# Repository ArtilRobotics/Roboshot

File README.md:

RoboShot
======================

Original project
here https://hectorbot.de/

Minimal Requirements 
---
	- RaspberryPi 3
	- Debian bases Linux (to use installscript)
    - Python 3.8

Prepare Raspberry
---
Activate I2C:

    sudo raspi-config 

Here go to "Interfacing Options" and Activate/Enable I2C 

PWM update:
----
Since this library and the onboard Raspberry Pi audio both use the PWM, they cannot be used together. You will need to blacklist the Broadcom audio kernel module by creating a file /etc/modprobe.d/snd-blacklist.conf with:
    blacklist snd_bcm2835

If the audio device is still loading after blacklisting, you may also need to comment it out in the /etc/modules file.

On headless systems you may also need to force audio through hdmi Edit config.txt and add:

    hdmi_force_hotplug=1
    hdmi_force_edid_audio=1
don't force if you have screen with the flex port.

Install on RaspberryPi
----
First you have to clone the github repo of Hector

	git clone https://github.com/H3c702/Hector9000.git

This repository doesn't contain a frontent. To get the original Hector9000 frontend see: 

	https://github.com/H3c702/Hector9000WebUI

To start the Hector software first move into the directory:

	cd Hector9000

Then run this command to setup all necessary tools:

	./setup.sh

Or run it with the option "-c" to preset the mqtt preconfigure for the WebUI

	./setup.sh -c

To start the software run:

	./start.sh

Add Drinks
---

To add a new Drink you have to modify the `drinks.py` file and add a new item into the `drink_list` array formatted as followed:

	{
        "name": "NAME OF DRINK",
        "recipe": [
            ("ingr", "INGREDIENT1", AMOUNT1),
            ("ingr", "INGREDIENT2", AMOUNT2)
        ]	
    }

All strings in `UPPERCASE` are placeholders, all lowercase strings have to be used literally in the definition. The `INGREDIENTx` names are not cleartext but are identifiers referencing into the `ingredients` list below in the same file. The `AMOUNTx` values are numerical values of the corresponding ingredient's amount in grams.

At the moment there are only some ingredients but feel free to put in some new. You can add them in src/Hector/conf/database.py .
Or you can use the WebUI when it is implemented.

A future extension might allow multi-language UIs.

Add Ingredients
---
To edit the Ingredients that can be used you can edit the 
database.py or use the tool in the tools folder.

    python3 Hector9000/tools/Editingredients.py

Assigning valves
---
The available ingredients are also moved to the db and can initial be edited in the databas.py 
or over the WEB UI in the future.

For the meantime you can use the script "SetValveIng.py".

    python3 Hector9000/tools/SetValveIng.py

Development on non-Hector hardware :
---

In the `HectorServer.py` you have to comment line :
	
	#from HectorHardware import HectorHardware as Hector

and uncomment:

	from HectorSimulator import HectorSimulator as Hector

## Info 

If you have some ideas or a fix or something else to make 
Hector better, don't be afraid to send us a pullrequest ;-)

---
Special thanks to
<div>
  <a>
   Hector 9000 Team
	git clone https://github.com/H3c702/Hector9000.git
  </a>

</div>

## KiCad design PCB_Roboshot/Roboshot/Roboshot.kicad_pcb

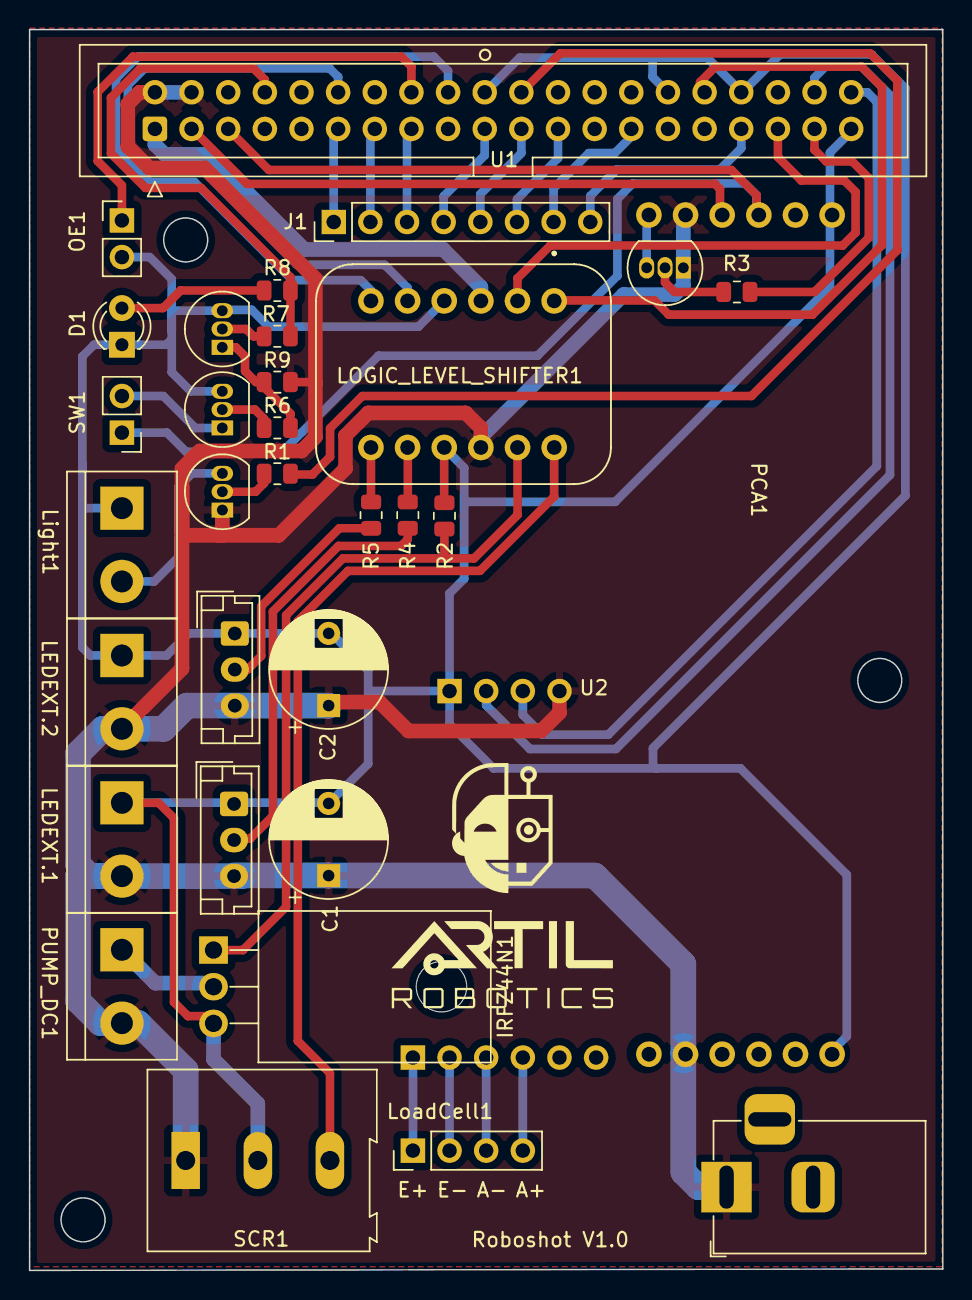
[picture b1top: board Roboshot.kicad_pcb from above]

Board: 2 copper layers, 63.3 x 86.0 mm, 33 parts (0 on the bottom side), 44 nets.

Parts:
B.OUTPUT1: BC546; TO-92_Inline
BUTTON1: BC546; TO-92_Inline
C1, C2: C_Polarized; CP_Radial_D8.0mm_P5.00mm
D1: LED; LED_D3.0mm
Ext.Source1: Conn_01x02; BarrelJack_Horizontal
IRFZ44N1: BSP89; TO-220F-3_Horizontal_TabDown
J1: Conn_01x08; PinHeader_1x08_P2.54mm_Vertical
LEDEXT.1, LEDEXT.2: Conn_01x02; TerminalBlock_bornier-2_P5.08mm
LEDSIGN1, LEDSIGN2: Conn_01x03; JST_EH_B3B-EH-A_1x03_P2.50mm_Vertical
LOGIC_LEVEL_SHIFTER1: Logic_Level_Shifter; Elevador_voltaje
Light1: Conn_01x02; TerminalBlock_bornier-2_P5.08mm
LoadCell1: Conn_01x04; PinHeader_1x04_P2.54mm_Vertical
OE1: Conn_01x02; PinHeader_1x02_P2.54mm_Vertical
PCA1: 815; PCA9685
PUMP_DC1: Conn_01x02; TerminalBlock_bornier-2_P5.08mm
Q1_LIGHT1: BC546; TO-92_Inline
Q_PCA1: BC546; TO-92_Inline
R1, R2, R3, R4, R5, R6, R7, R8, R9: R; R_0805_2012Metric
SCR1: Conn_01x03; TerminalBlock_Altech_AK300-3_P5.00mm
SW1: SW_Push_Dual_x2; PinHeader_1x02_P2.54mm_Vertical
U1: 7840-0000PR; IDC-Header_2x20_P2.54mm_Vertical
U2: H; Dual Channel

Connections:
+3V3: LOGIC_LEVEL_SHIFTER1.LV, U1.1, U1.17
+5V: C1.1, C2.1, Ext.Source1.1, LEDEXT.1.2, LEDEXT.2.2, LEDSIGN1.3, LEDSIGN2.3, LOGIC_LEVEL_SHIFTER1.HV, PCA1.VCC_1 (VCC), PCA1.VCC_2 (VCC), PUMP_DC1.2, Q1_LIGHT1.1 (C), Q_PCA1.1 (C), R9.2, SCR1.1, U1.2, U1.4, U2.VCC
/2N_PCA9685: PCA1.V+_1 (V+), PCA1.V+_2 (V+), Q_PCA1.3 (E)
/A+: LoadCell1.4, U2.A+
/A-: LoadCell1.3, U2.A-
/Button_OUTPUT: B.OUTPUT1.1 (C), SW1.2 (D)
/E+: LoadCell1.1, U2.E+
/E-: LoadCell1.2, U2.E-
/GPIO2(SDA1): PCA1.SDA_1 (SDA), PCA1.SDA_2 (SDA), U1.3
/GPIO3(SCL1): PCA1.SCL_1 (SCL), PCA1.SCL_2 (SCL), SW1.1 (C), U1.5
/GPIO9(SPI0_MISO): J1.5, U1.21
/GPIO10(SPI0_MOSI): J1.4, U1.19
/GPIO11(SPI0_SCK): J1.6, U1.23
/GPIO12(PWM0): LOGIC_LEVEL_SHIFTER1.LV1, U1.32
/GPIO13(PWM1): J1.8, U1.33
/GPIO14(TXD0): R7.1, R8.1, U1.8
/GPIO17(GEN0): J1.1, U1.11
/GPIO18(GEN1)(PWM0): LOGIC_LEVEL_SHIFTER1.LV3, U1.12
/GPIO19(SPI1_MISO): LOGIC_LEVEL_SHIFTER1.LV2, U1.35
/GPIO20(SPI1_MOSI): U1.38, U2.DT
/GPIO21(SPI1_SCK): U1.40, U2.SCK
/GPIO22(GEN3): J1.3, U1.15
/GPIO23(GEN4): OE1.1, U1.16
/GPIO24(GEN5): LOGIC_LEVEL_SHIFTER1.LV4, U1.18
/GPIO25(GEN6): R1.1, U1.22
/GPIO26: R3.1, U1.37
/GPIO27(GEN2): J1.2, U1.13
/HV1: LOGIC_LEVEL_SHIFTER1.HV3, R4.1
/HV2: IRFZ44N1.1 (G), LOGIC_LEVEL_SHIFTER1.HV2, R2.1
/HV3: LOGIC_LEVEL_SHIFTER1.HV4, R5.1
/HV4: LOGIC_LEVEL_SHIFTER1.HV1, SCR1.3
/ID_SD: J1.7, U1.27
/Inv.OUPUT: BUTTON1.1 (C), R6.1, R9.1
/LIGHT: Light1.2, Q1_LIGHT1.3 (E)
/PUMP: IRFZ44N1.2 (D), PUMP_DC1.1
GND: B.OUTPUT1.3 (E), BUTTON1.3 (E), C1.2, C2.2, D1.1 (K), Ext.Source1.2, IRFZ44N1.3 (S), LEDEXT.1.1, LEDEXT.2.1, LEDSIGN1.1, LEDSIGN2.1, LOGIC_LEVEL_SHIFTER1.GND, Light1.1, OE1.2, PCA1.GND_1 (GND), PCA1.GND_2 (GND), R2.2, SCR1.2, U1.6, U1.9, U1.14, U1.20, U1.25, U1.30, U1.34, U1.39, U2.GND
unnamed: B.OUTPUT1.2 (B), R6.2
unnamed: BUTTON1.2 (B), R7.2
unnamed: D1.2 (A), R8.2
unnamed: LEDSIGN1.2, R4.2
unnamed: LEDSIGN2.2, R5.2
unnamed: PCA1.OE_1 (~OE), PCA1.OE_2 (~OE)
unnamed: Q1_LIGHT1.2 (B), R1.2
unnamed: Q_PCA1.2 (B), R3.2

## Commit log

2022-07-21 test
2022-07-21 sigo probando
2022-07-21 probando antonio compu
2022-07-21 new branch
2022-07-21 branch 2
2022-07-21 master branch
2022-07-21 cambioi en master
2022-07-22 Hola con Josue
2022-07-22 Validado HectorHardware.py
2022-07-22 Valve dose recontra probado
2022-07-23 Probando tira led aparte
2022-07-23 Probando tira led
2022-07-23 Barra Led funcionando
2022-07-24 read me update
2022-07-24 update readme wit pwm config
2022-07-24 SimpleLed Tests
2022-07-24 mqtt check conection
2022-07-27 Añadir PCB falta hacer cambios
2022-07-27 Comentario en Controller
2022-07-29 Diseño terminado
2022-08-01 Placa finalizada
2022-08-05 Placa_roboshot
2022-08-09 PCB_final
2022-09-14 Cambios en PCB roboshot_final
2022-09-20 Agregado para que se prenda el transistor
2022-09-21 Cambio a GPIO26
2022-09-21 Cambio a GPIO26 par PCA9685
2022-09-26 Placa final_Roboshot
2022-09-27 Placa_reducida tamaño
2022-10-03 Cambios para probar el Hector Simulator
2022-10-03 Cambio en Hector Server
2022-10-03 Cambio a 0 otra vez
2022-10-10 revision de PCB
2022-10-14 Agregar imagenes_By me_Data_By Lizpy
2022-10-14 Agrego imagen a Data_set cocteles de MMWINGS
2022-10-15 Agregar imagenes Hector 9000
2022-12-01 zero de servos
2022-12-07 Cambios en placa para china y para artesanal
2022-12-15 configuracion servos
2022-12-27 Defini Valores en resistencia y arregle el problema el InvPin en el boton de Power
2023-01-23 Roboshot_without_servo's lights
2023-01-24 chore!: Led_standart ok, Led_Servos not yet, ing
2023-01-30 core:! imageupload_equationdefine
2023-02-03 Cambiado el database y las recetas de MM Wings
2023-02-03 Ecuacion hasta 180 ml
2023-02-03 Imagenes de 5 cocteles_recetas_LEDout
2023-02-08 Error_2ml
2023-02-22 Final
2023-03-13 Before_valvedose_modified
2023-03-22 Just_one_tare_at the beginning
